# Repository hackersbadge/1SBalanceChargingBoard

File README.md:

# 1S LiHv/LiPo Balance Charging Board

- [x] Hardware: WhiteA10n3

How to charge

Charger setup: Balance charge 6 x 1s 450Mah Battries

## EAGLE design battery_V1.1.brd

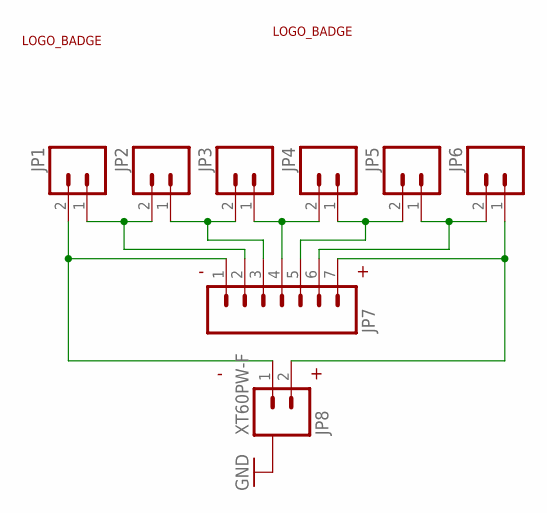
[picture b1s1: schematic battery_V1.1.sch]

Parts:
JP1, JP2, JP3, JP4, JP5, JP6: M02_PH2.0_Z; PH2.0_2Z
JP7: M07_XH2.54_7Z; XH2.54_7Z
JP8: XT60PW-F
U1: LOGO_BADGE_24.3_20_S
U2: LOGO_BADGE_12.2_9.5_S

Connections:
GND: JP8.P$1 (G), JP8.P$2 (G), JP8.P$3 (G), JP8.P$4 (G)
unnamed: JP1.1, JP2.2, JP7.2
unnamed: JP2.1, JP3.2, JP7.3
unnamed: JP3.1, JP4.2, JP7.4
unnamed: JP4.1, JP5.2, JP7.5
unnamed: JP5.1, JP6.2, JP7.6
unnamed: JP6.1, JP7.7, JP8.2
unnamed: JP1.2, JP7.1, JP8.1

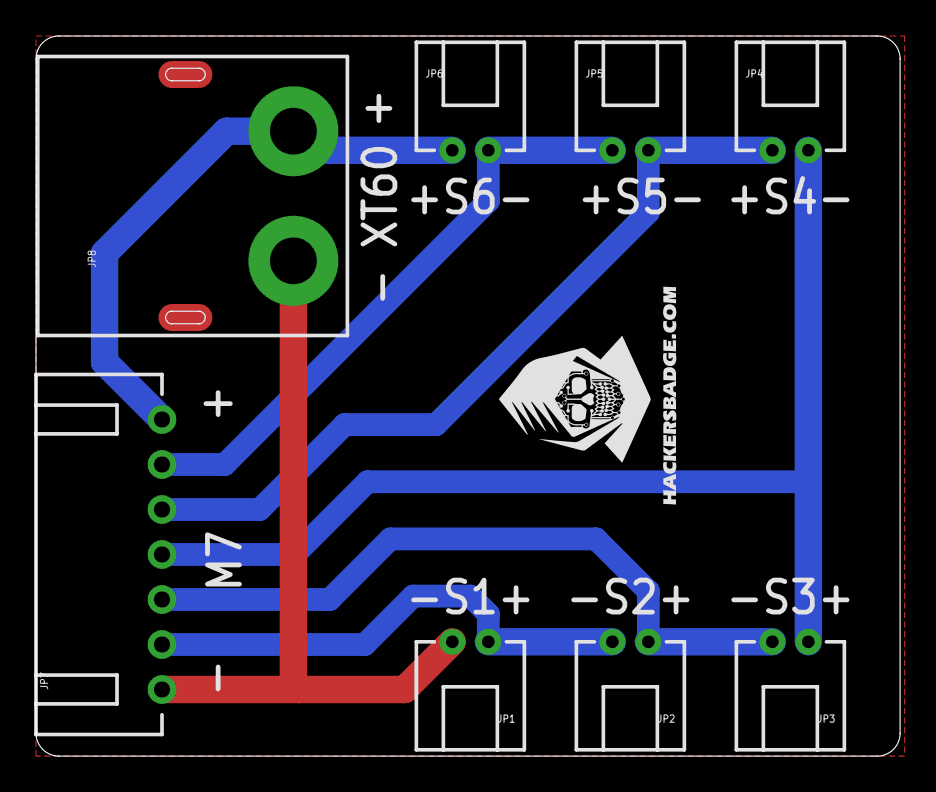
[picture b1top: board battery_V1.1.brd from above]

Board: 2 copper layers, 48.0 x 40.0 mm, 10 parts (1 on the bottom side), 8 nets.

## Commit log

2021-07-02 add pictures
2021-07-02 add battery_V1.1.gkm

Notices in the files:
parts and their libraries:
2SparkFun: Licensing: CC v3.0 Share-Alike You are welcome to use this library for commercial purposes.
